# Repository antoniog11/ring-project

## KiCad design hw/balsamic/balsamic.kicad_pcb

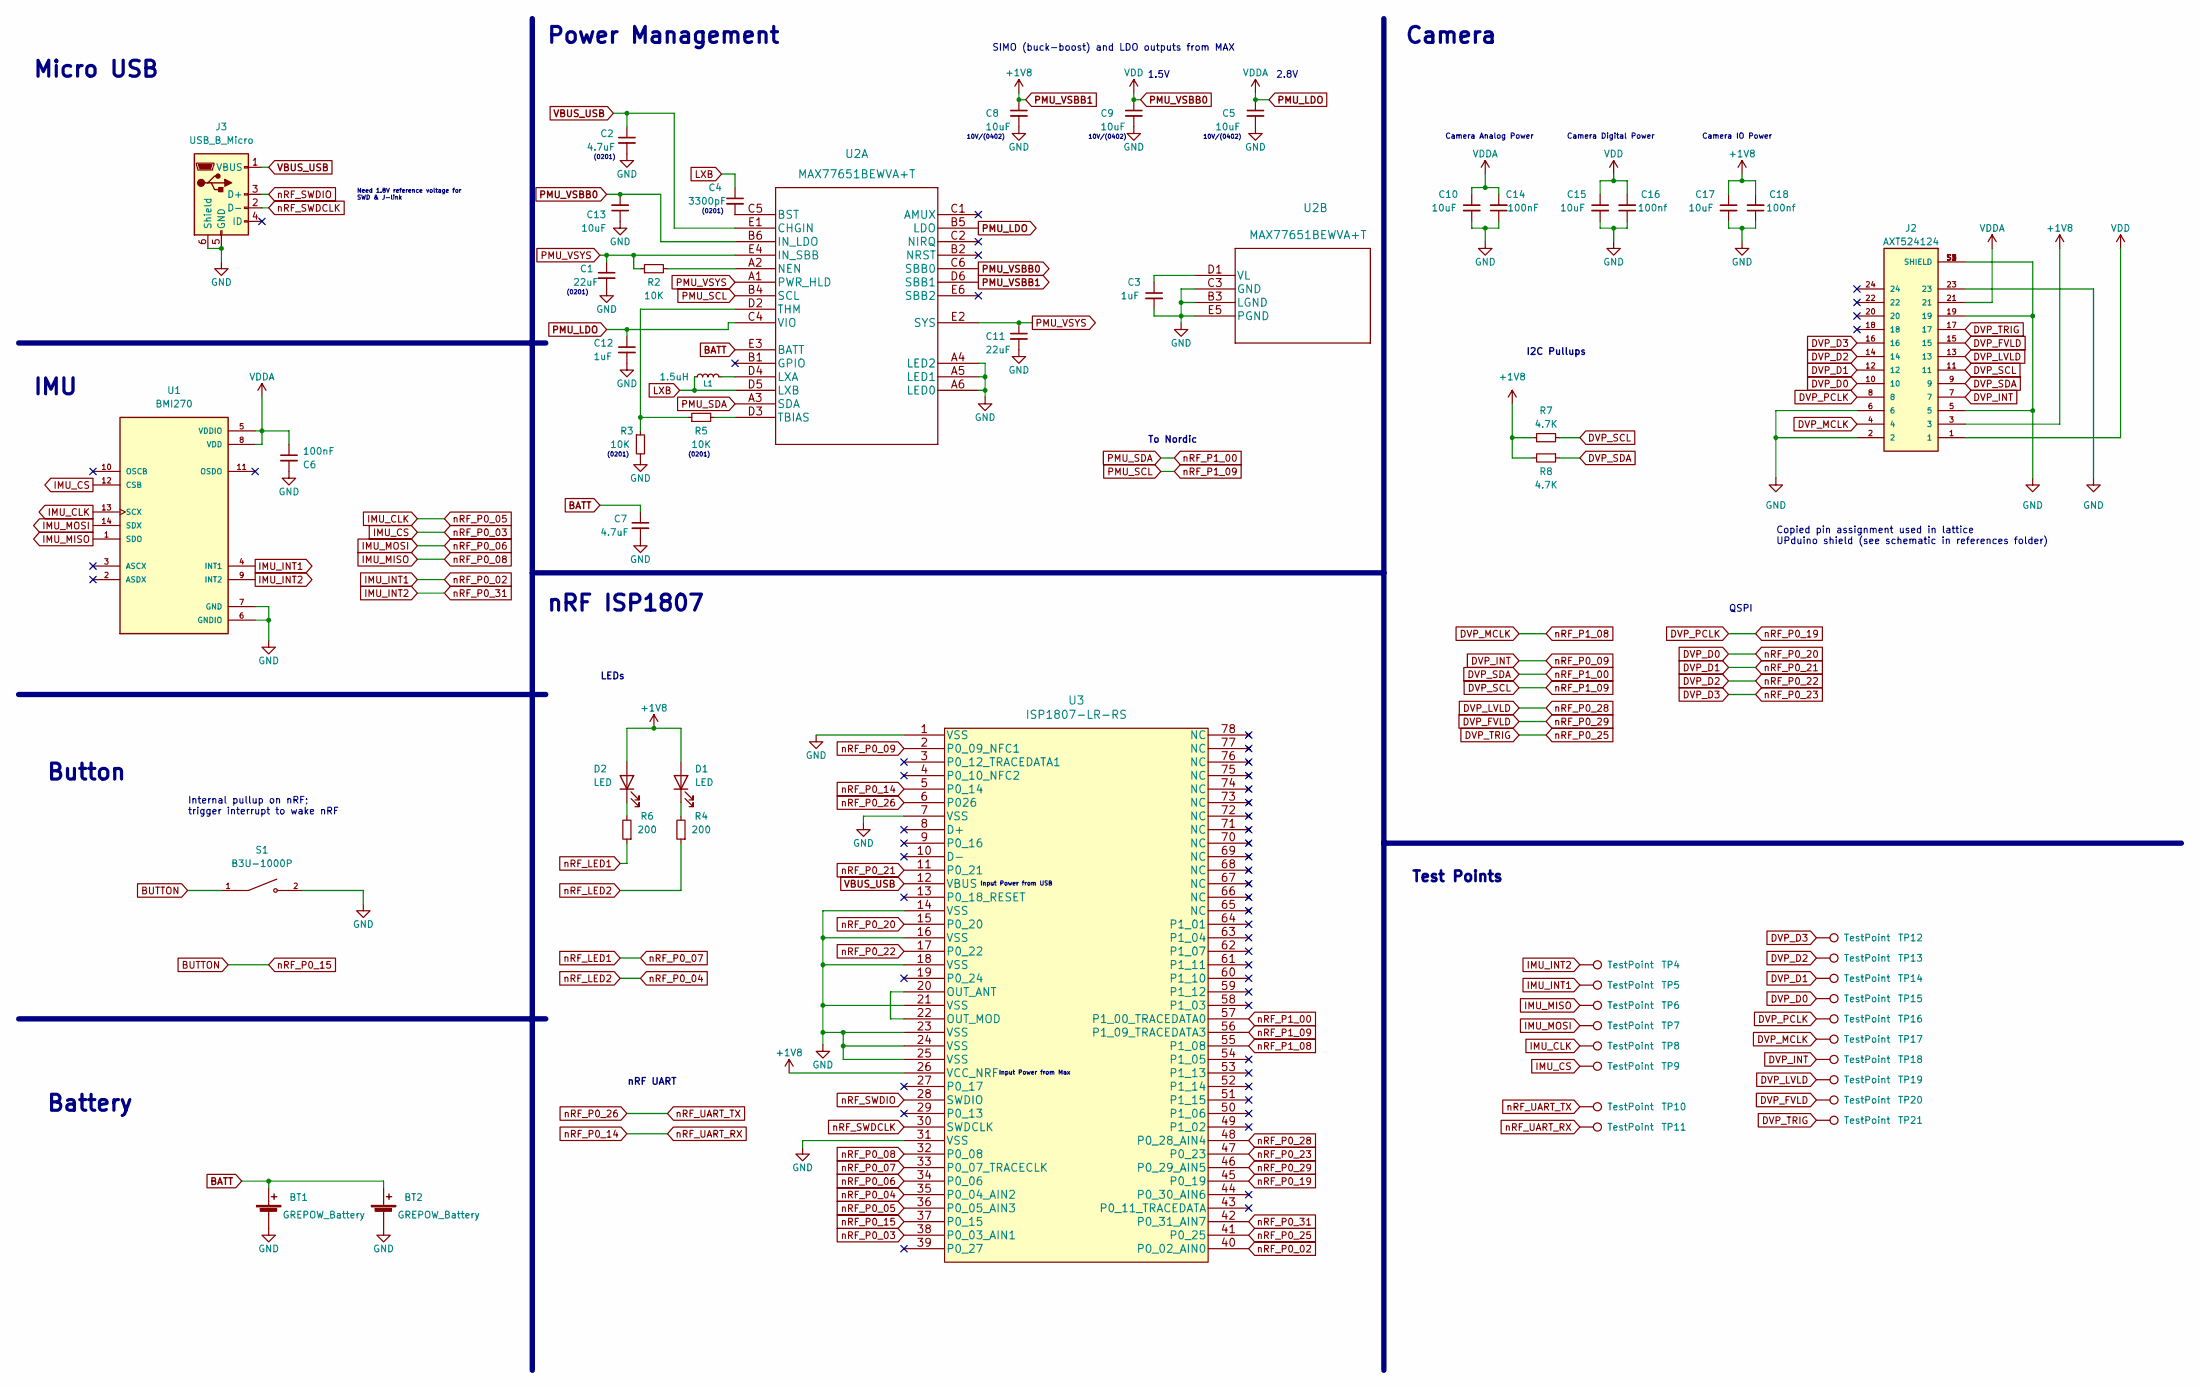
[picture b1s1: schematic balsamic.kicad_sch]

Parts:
BT1, BT2: GREPOW_Battery; balsamic_grepow_battery
C1, C11: 22uF; C_0201_0603Metric
C2, C7: 4.7uF; C_0201_0603Metric
C3, C12: 1uF; C_0201_0603Metric
C4: 3300pF; C_0201_0603Metric
C5, C8, C9, C10, C13, C15, C17: 10uF; C_0201_0603Metric
C6, C14: 100nF; C_0201_0603Metric
C16, C18: 100nf; C_0201_0603Metric
D1, D2: LED; LED_0402_1005Metric
J2: AXT524124; PANASONIC_AXT524124
J3: USB_B_Micro; USB_Micro-B_GCT_USB3076-30-A
L1: 1.5uH; L_0805_2012Metric
R2, R3, R5: 10K; R_0201_0603Metric
R4, R6: 200; R_0201_0603Metric
R7, R8: 4.7K; R_0201_0603Metric
S1: B3U-1000P; SW_B3U-1000P
TP4, TP5, TP6, TP7, TP8, TP9, TP10, TP11, TP12, TP13, TP14, TP15, TP16, TP17, TP18, TP19, TP20, TP21: TestPoint; TestPoint_Pad_D0.5mm
U1: BMI270; XDCR_BMI270
U2: MAX77651BEWVA+T; MAX77651BEWVA&plus_T
U3: ISP1807-LR-RS

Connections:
BATT: BT1.1 (+), BT2.1 (+), C7.1, U2.E3 (BATT)
BUTTON: S1.1, U3.37 (P0_15)
DVP_D0: J2.10, TP15.1, U3.15 (P0_20)
DVP_D1: J2.12, TP14.1, U3.11 (P0_21)
DVP_D2: J2.14, TP13.1, U3.17 (P0_22)
DVP_D3: J2.16, TP12.1, U3.47 (P0_23)
DVP_FVLD: J2.15, TP20.1, U3.46 (P0_29_AIN5)
DVP_INT: J2.7, TP18.1, U3.2 (P0_09_NFC1)
DVP_LVLD: J2.13, TP19.1, U3.48 (P0_28_AIN4)
DVP_MCLK: J2.4, TP17.1, U3.55 (P1_08)
DVP_PCLK: J2.8, TP16.1, U3.45 (P0_19)
DVP_SCL: J2.11, R7.2, U2.B4 (SCL), U3.56 (P1_09_TRACEDATA3)
DVP_SDA: J2.9, R8.1, U2.A3 (SDA), U3.57 (P1_00_TRACEDATA0)
DVP_TRIG: J2.17, TP21.1, U3.41 (P0_25)
GND: BT1.2 (-), BT2.2 (-), C1.2, C2.2, C3.2, C5.2, C6.2, C7.2, C8.2, C9.2, C10.2, C11.2, C12.2, C13.1, C14.1, C15.2, C16.1, C17.2, C18.1, J2.2, J2.5, J2.6, J2.19, J2.23, J2.S1 (SHIELD), J2.S2 (SHIELD), J2.S3 (SHIELD), J2.S4 (SHIELD), J3.5 (GND), J3.6 (Shield), R3.2, S1.2, U1.6 (GNDIO), U1.7 (GND), U2.A4 (LED2), U2.A5 (LED1), U2.A6 (LED0), U2.B3 (LGND), U2.C3 (GND), U2.E5 (PGND), U3.1 (VSS), U3.7 (VSS), U3.14 (VSS), U3.16 (VSS), U3.18 (VSS), U3.21 (VSS), U3.23 (VSS), U3.24 (VSS), U3.25 (VSS), U3.31 (VSS)
IMU_CLK: TP8.1, U1.13 (SCX), U3.36 (P0_05_AIN3)
IMU_CS: TP9.1, U1.12 (CSB), U3.38 (P0_03_AIN1)
IMU_INT1: TP5.1, U1.4 (INT1), U3.40 (P0_02_AIN0)
IMU_INT2: TP4.1, U1.9 (INT2), U3.42 (P0_31_AIN7)
IMU_MISO: TP6.1, U1.1 (SDO), U3.32 (P0_08)
IMU_MOSI: TP7.1, U1.14 (SDX), U3.34 (P0_06)
LXB: C4.1, L1.1, U2.D5 (LXB)
unnamed: C3.1, U2.D1 (VL)
unnamed: C4.2, U2.C5 (BST)
unnamed: D1.1 (K), R4.2
unnamed: D2.1 (K), R6.2
unnamed: L1.2, U2.D4 (LXA)
unnamed: R2.2, U2.A2 (NEN)
unnamed: R3.1, R5.1, U2.D2 (THM)
unnamed: R5.2, U2.D3 (TBIAS)
unnamed: U3.20 (OUT_ANT), U3.22 (OUT_MOD)
PMU_LDO: C5.1, C6.1, C10.1, C12.1, C14.2, J2.21, U1.5 (VDDIO), U1.8 (VDD), U2.B5 (LDO), U2.C4 (VIO)
PMU_VSBB0: C9.1, C13.2, C15.1, C16.2, J2.1, U2.B6 (IN_LDO), U2.C6 (SBB0)
PMU_VSBB1: C8.1, C17.1, C18.2, D1.2 (A), D2.2 (A), J2.3, R7.1, R8.2, U2.D6 (SBB1), U3.26 (VCC_NRF)
PMU_VSYS: C1.1, C11.1, R2.1, U2.A1 (PWR_HLD), U2.E2 (SYS), U2.E4 (IN_SBB)
VBUS_USB: C2.1, J3.1 (VBUS), U2.E1 (CHGIN), U3.12 (VBUS)
nRF_LED1: R6.1, U3.33 (P0_07_TRACECLK)
nRF_LED2: R4.1, U3.35 (P0_04_AIN2)
nRF_P0_14: TP11.1, U3.5 (P0_14)
nRF_P0_26: TP10.1, U3.6 (P026)
nRF_SWDCLK: J3.2 (D-), U3.30 (SWDCLK)
nRF_SWDIO: J3.3 (D+), U3.28 (SWDIO)

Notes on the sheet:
2.8V
Battery
Button
10V/(0402)
1.5V
Camera IO Power
Input Power from USB
Input Power from Max
Test Points
(0201)
To Nordic
Camera Digital Power
nRF ISP1807
Micro USB
Internal pullup on nRF; trigger interrupt to wake nRF
SIMO (buck-boost) and LDO outputs from MAX
Copied pin assignment used in lattice UPduino shield (see schematic in references folder)
Camera Analog Power
LEDs
nRF UART
QSPI
Camera
I2C Pullups
Need 1.8V reference voltage for SWD & J-link
IMU
Power Management

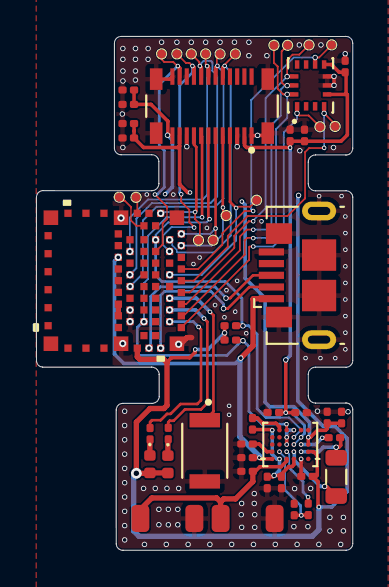
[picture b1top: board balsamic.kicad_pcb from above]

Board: 4 copper layers, 17.6 x 28.5 mm, 54 parts (0 on the bottom side), 42 nets.

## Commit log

2022-09-16 Add time to first prediction
2022-09-28 Maix-LogoClassifier working
2022-10-24 Axelerate and HW schematic files
2022-10-24 Adding micropython scripts
2022-10-25 HW files
2022-11-03 Add hardware files
2023-01-27 PCB Schematic Layout
    Finished schematic layout for MAX77658, power input to kendryte and some
    of the signals for the kendryte IO.
    I am beginning the layout for the ISP.
2023-01-31 Schematic layout v0.1
2023-01-31 fixed .gitignore files and added kicad ignored files
2023-02-21 Removed CH552T for programming
2023-02-24 Made some updates to schematic USB C and power
2023-02-28 Began board Layout
2023-03-02 Board layout v.1
2023-03-28 ignored .DS_Store
2023-03-28 Reduced spacing between ICs
2023-03-30 began shrinking board w/out K210
2023-03-30 updated gitignore
2023-03-30 Deleted .DS_Store
2023-03-30 Removed redundant libraries directory
2023-03-31 switched to mezzanine camera connector
2023-03-31 Added kicad symbols and footprints
    - Added TestPoint footprints from Maruchi
    - Added symbols and footprints for power management ICs from maxim
2023-03-31 changed PMU to MAX77651
2023-04-11 Got board size to 16.1x9.825mm
2023-04-13 Added symbols and 3D models. Edited schematic
2023-04-14 Began 2 layer-routing
2023-04-20 Added connector to replace micro-USB
2023-04-20 Added button symbol and footprint
2023-04-20 Began layout of flex-pcb
2023-04-27 Added smaller button footprints
2023-04-27 First full routing attempt
    - Switched to using a 4 layer board on the islands.
2023-05-04 incorporated Malik's board feedback

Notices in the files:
parts and their libraries:
Copyright 2021 Accelerated Designs. All rights reserved.
